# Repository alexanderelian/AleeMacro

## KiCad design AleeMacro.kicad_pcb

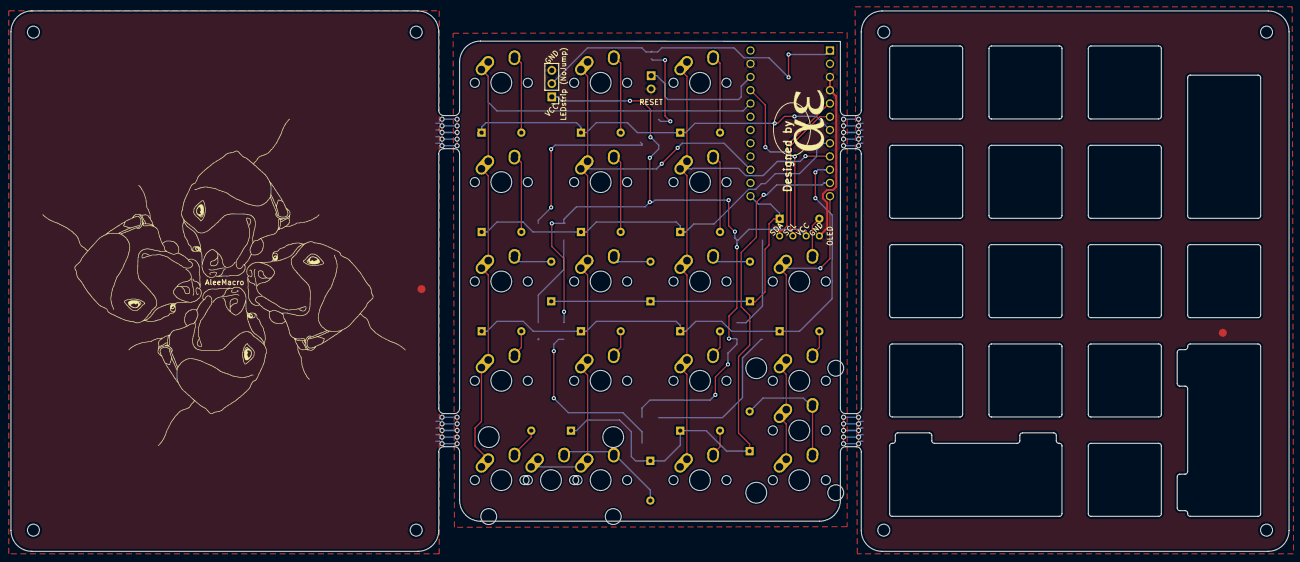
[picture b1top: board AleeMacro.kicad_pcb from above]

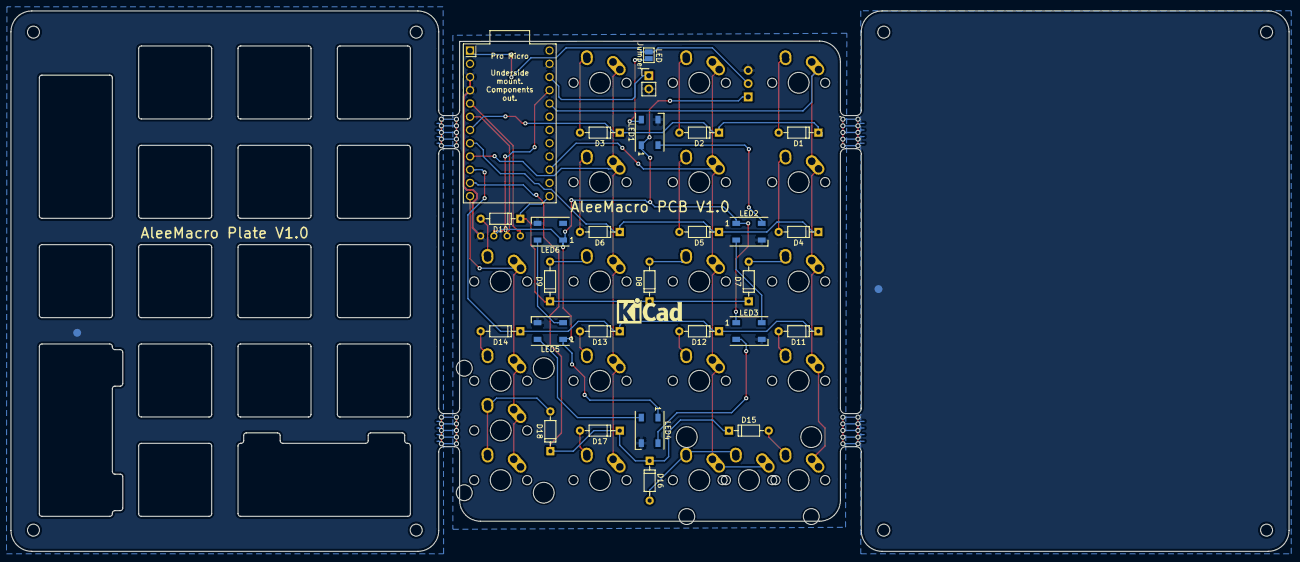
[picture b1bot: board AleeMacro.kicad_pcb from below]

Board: 2 copper layers, 245.1 x 103.6 mm, 58 parts (27 on the bottom side), 39 nets.

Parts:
D1, D2, D3, D4, D5, D6, D7, D8, D9, D10, D11, D12, D13, D14, D15, D16, D17, D18: 1N4148; D_DO-35_SOD27_P7.62mm_Horizontal
Jumper: Jumper_NO_Small; SolderJumper-2_P1.3mm_Open_Pad1.0x1.5mm
LED1, LED2, LED3, LED4, LED5, LED6: WS2812B; LED_WS2812B_PLCC4_5.0x5.0mm_P3.2mm
LEDstrip (NoJump): Conn_01x03_Male (LED STRIP); PinHeader_1x03_P2.54mm_Vertical
MOUSEBITE1, MOUSEBITE2, MOUSEBITE3, MOUSEBITE4, MOUSEBITE5, MOUSEBITE6, MOUSEBITE7, MOUSEBITE8: Mousebites; breakaway-mousebites
MX1, MX2, MX3, MX4, MX5, MX6, MX7, MX8, MX9, MX10, MX11, MX12, MX13, MX14, MX15, MX16, MX17, MX18: MX-1U; MX-1U-NoLED
MX16a, MX18a: MX-2U; MX-2U-ReversedStabilizers-NoLED
O1: Outline; outline
OLED: Conn_01x04_Male (OLED); OLED_v2
SW1: SW_Push; PinHeader_1x02_P2.54mm_Vertical
U1: ProMicro; ProMicro-EnforcedTop

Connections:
COL0: MX1.1, MX4.1, MX7.1, MX11.1, MX15.1, U1.20
COL1: MX2.1, MX5.1, MX8.1, MX12.1, MX16.1, MX16a.1, U1.15
COL2: MX3.1, MX6.1, MX9.1, MX13.1, MX17.1, U1.9
COL3: MX10.1, MX14.1, MX18.1, MX18a.1, U1.12
GND: LED1.3, LED2.3, LED3.3, LED4.3, LED5.3, LED6.3, LEDstrip (NoJump).3, OLED.1, SW1.2, U1.3, U1.4, U1.23
unnamed: D1.2, MX1.2
unnamed: D2.2, MX2.2
unnamed: D3.2, MX3.2
unnamed: D4.2, MX4.2
unnamed: D5.2, MX5.2
unnamed: D6.2, MX6.2
unnamed: D7.2, MX7.2
unnamed: D8.2, MX8.2
unnamed: D9.2, MX9.2
unnamed: D10.2, MX10.2
unnamed: D11.2, MX11.2
unnamed: D12.2, MX12.2
unnamed: D13.2, MX13.2
unnamed: D14.2, MX14.2
unnamed: D15.2, MX15.2
unnamed: D16.2, MX16.2, MX16a.2
unnamed: D17.2, MX17.2
unnamed: D18.2, MX18.2, MX18a.2
unnamed: Jumper.2, LEDstrip (NoJump).2, U1.1
unnamed: Jumper.1, LED1.4
unnamed: LED1.2, LED2.4
unnamed: LED2.2, LED3.4
unnamed: LED3.2, LED4.4
unnamed: LED4.2, LED5.4
unnamed: LED5.2, LED6.4
unnamed: SW1.1, U1.22
ROW0: D1.1, D2.1, D3.1, U1.7
ROW1: D4.1, D5.1, D6.1, U1.8
ROW2: D7.1, D8.1, D9.1, D10.1, U1.13
ROW3: D11.1, D12.1, D13.1, D14.1, U1.10
ROW4: D15.1, D16.1, D17.1, D18.1, U1.11
SCL: OLED.3, U1.6
SDA: OLED.4, U1.5
VCC: LED1.1, LED2.1, LED3.1, LED4.1, LED5.1, LED6.1, LEDstrip (NoJump).1, OLED.2, U1.21

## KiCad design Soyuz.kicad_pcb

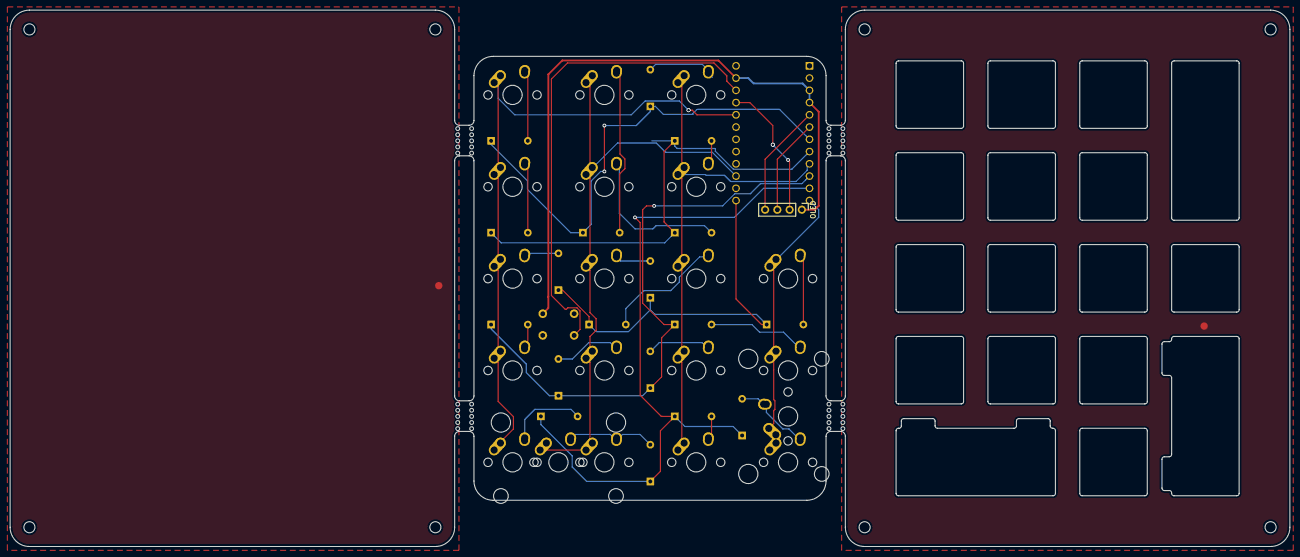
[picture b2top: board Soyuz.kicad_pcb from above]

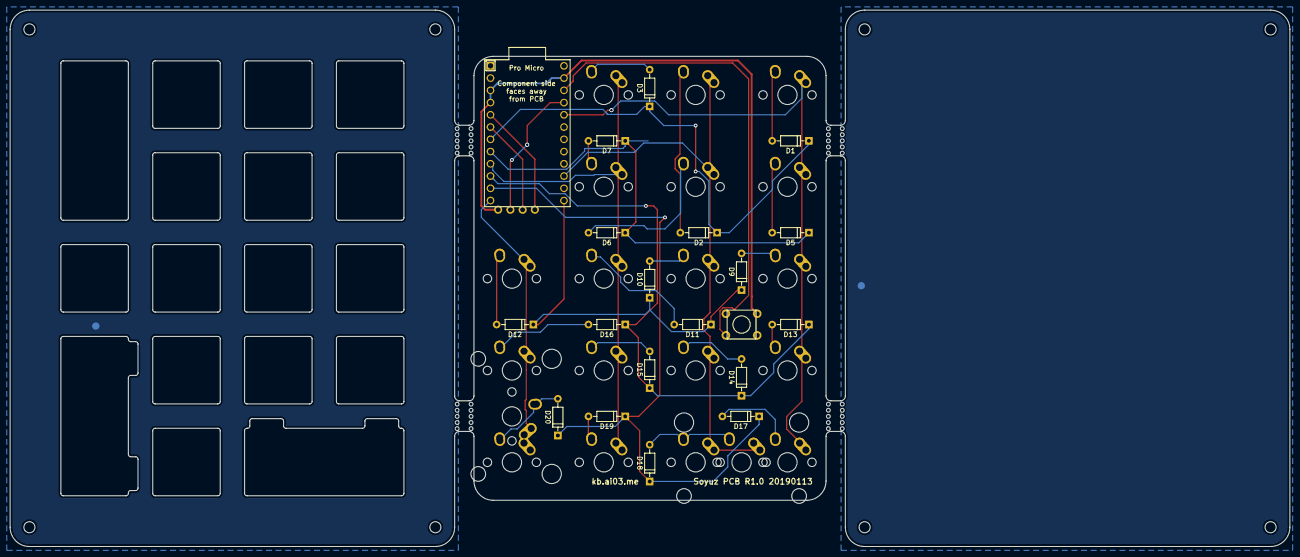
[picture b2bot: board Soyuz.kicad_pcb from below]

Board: 2 copper layers, 265.4 x 111.2 mm, 50 parts (20 on the bottom side), 32 nets.

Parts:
D1, D2, D3, D5, D6, D7, D9, D10, D11, D12, D13, D14, D15, D16, D17, D18, D19, D20: 1N4148; D_DO-35_SOD27_P7.62mm_Horizontal
MOUSEBITE1, MOUSEBITE2, MOUSEBITE3, MOUSEBITE4, MOUSEBITE5, MOUSEBITE6, MOUSEBITE7, MOUSEBITE8: Mousebites; breakaway-mousebites
MX1, MX2, MX3, MX5, MX6, MX7, MX10, MX11, MX12, MX13, MX14, MX15, MX16, MX17, MX19, MX20, MX21, MX22: MX-1U; MX-1U-NoLED
MX18, MX23: MX-2U; MX-2U-ReversedStabilizers-NoLED
O1: Outline; outline
OLED: Conn_01x04_Male (OLED); PinHeader_1x04_P2.54mm_Vertical
SW1: SW_Push; PushButton_6x6mm_TH_Pretty
U1: ProMicro; ProMicro-EnforcedTop

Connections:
COL0: MX1.1, MX5.1, MX10.1, MX14.1, MX19.1, U1.20
COL1: MX2.1, MX6.1, MX11.1, MX15.1, MX20.1, MX23.1, U1.15
COL2: MX3.1, MX7.1, MX12.1, MX16.1, MX21.1, U1.9
COL3: MX13.1, MX17.1, MX18.1, MX22.1, U1.12
GND: OLED.1, SW1.2, U1.3, U1.4, U1.23
unnamed: D1.2, MX1.2
unnamed: D2.2, MX2.2
unnamed: D3.2, MX3.2
unnamed: D5.2, MX5.2
unnamed: D6.2, MX6.2
unnamed: D7.2, MX7.2
unnamed: D9.2, MX10.2
unnamed: D10.2, MX11.2
unnamed: D11.2, MX12.2
unnamed: D12.2, MX13.2
unnamed: D13.2, MX14.2
unnamed: D14.2, MX15.2
unnamed: D15.2, MX16.2
unnamed: D16.2, MX17.2
unnamed: D17.2, MX19.2
unnamed: D18.2, MX20.2, MX23.2
unnamed: D19.2, MX21.2
unnamed: D20.2, MX18.2, MX22.2
unnamed: SW1.1, U1.22
ROW0: D1.1, D2.1, D3.1, U1.7
ROW1: D5.1, D6.1, D7.1, U1.8
ROW2: D9.1, D10.1, D11.1, D12.1, U1.13
ROW3: D13.1, D14.1, D15.1, D16.1, U1.10
ROW4: D17.1, D18.1, D19.1, D20.1, U1.11
SCL: OLED.3, U1.6
SDA: OLED.4, U1.5
VCC: OLED.2, U1.21

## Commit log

2021-06-23 Macropad Files
2021-06-24 OLED footprint fixed
2021-06-24 Diodes Moved & ProM Position
2021-06-25 Named and Logo Imported
2021-07-01 Ground Fills Added & Edges Thinned
2021-07-01 Edgecut and Standoff clearence - Solved
2021-07-02 Designs added
2021-07-02 Plate Design Updated
2021-07-03 Improved diode placement and Routing
2021-07-03 Add Submodules
2021-07-06 Routing Adjustments
2021-07-09 More routing and silks
2021-07-11 Mounting Aligned (Guide lines to be removed)
2021-07-27 Gerbers
2021-08-23 LEDS added
2021-08-26 LED Traces Confirmed
2021-08-28 Prototype Run 1
